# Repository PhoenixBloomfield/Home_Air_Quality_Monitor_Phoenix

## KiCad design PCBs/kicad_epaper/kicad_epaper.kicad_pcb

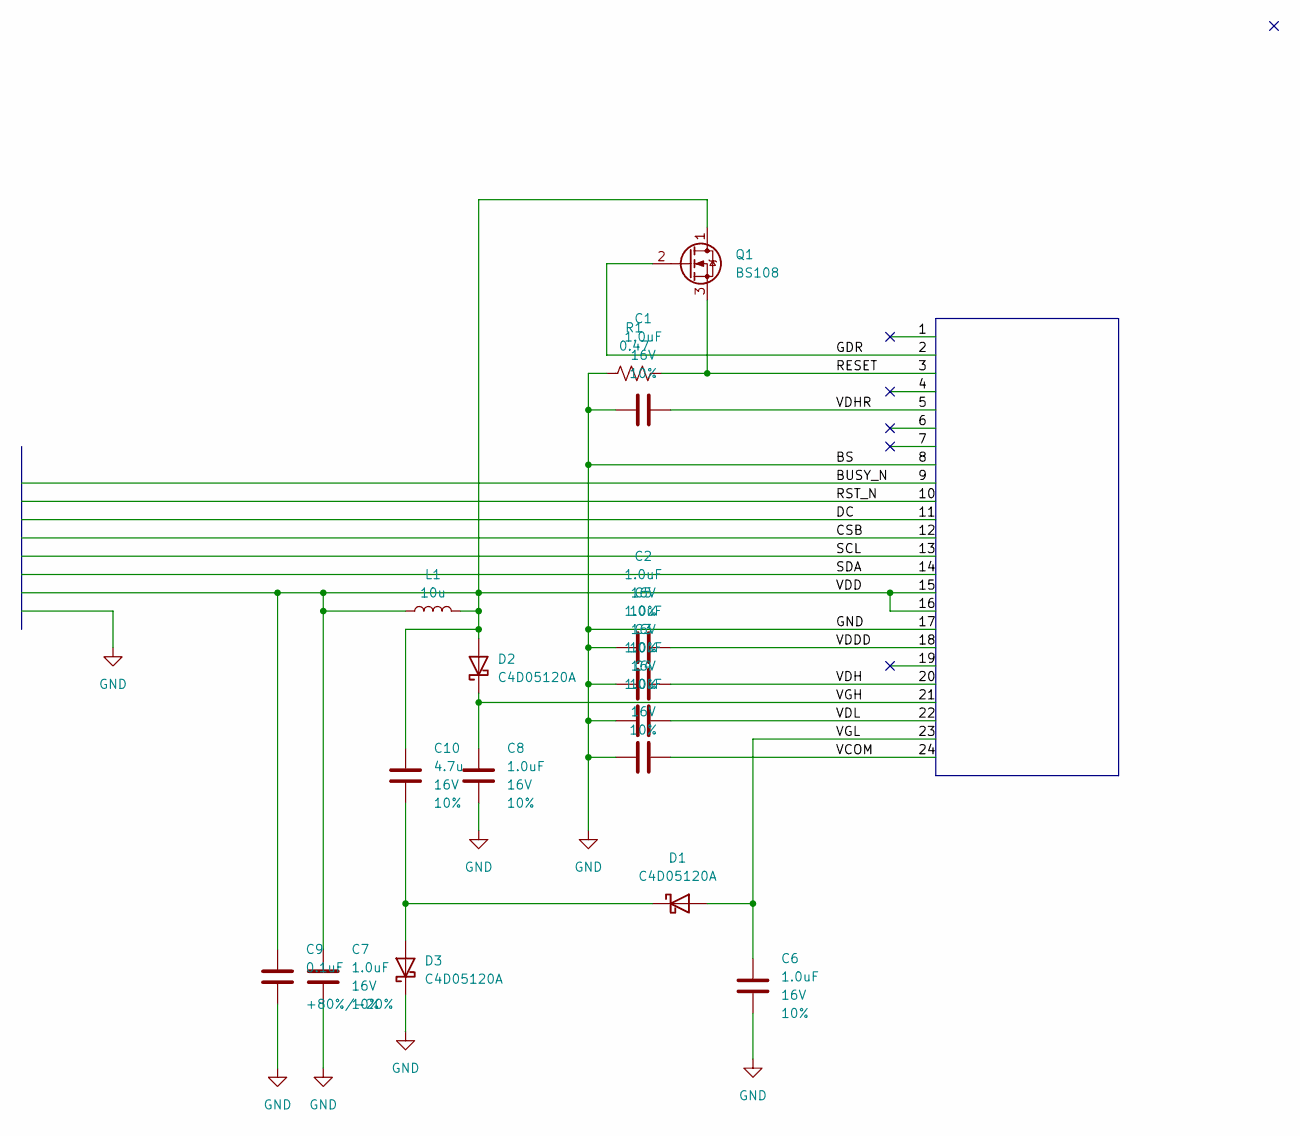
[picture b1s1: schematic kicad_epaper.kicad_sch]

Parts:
C1, C2, C3, C4, C5, C6, C7, C8: 1.0uF; C_0603_1608Metric; Voltage 16V; Tolerance 10%
C9: 0.1uF; C_0603_1608Metric; Voltage 25V; Tolerance +80%/-20%
C10: 4.7u; C_0603_1608Metric; Voltage 16V; Tolerance 10%
D1, D2, D3: C4D05120A; TO-220-2_Vertical
L1: 10u
Q1: BS108; TO-92_Inline
R1: 0.47; R_0603_1608Metric

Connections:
/2: Q1.2 (G)
/3: Q1.3 (S), R1.2
/5: C1.2
/15: C7.1, C9.1, C10.1, D2.2 (A), L1.1, L1.2, Q1.1 (D)
/18: C2.1
/20: C5.1
/21: C8.1, D2.1 (K)
/22: C3.1
/23: C6.1, D1.2 (A)
/24: C4.1
GND: C1.1, C2.2, C3.2, C4.2, C5.2, C6.2, C7.2, C8.2, C9.2, D3.1 (K), R1.1
unnamed: C10.2, D1.1 (K), D3.2 (A)

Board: 2 copper layers, 15 parts (0 on the bottom side), 6 nets, no tracks yet.

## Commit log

2023-11-30 kicad screen PCB
